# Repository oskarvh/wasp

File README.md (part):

# wasp

**WebAssembly Swarm Processor** — a WAMR network compute distribution for MCUs.

A *wasp node* is a deliberately dumb MCU: it boots Zephyr, joins the network,
and waits. A *coordinator* (future work, not in this repo yet) pushes
WebAssembly modules and execution commands to nodes over a TCP socket. The
node loads the module into the [WebAssembly Micro Runtime
(WAMR)](https://github.com/bytecodealliance/wasm-micro-runtime), executes it,
and reports results back. All application intelligence lives in the WASM
modules and the coordinator — the firmware is a thin, portable execution
shell.

```
┌─────────────┐        TCP / framed protocol         ┌──────────────────────┐
│ Coordinator │ ───────────────────────────────────▶ │  wasp node (MCU)     │
│ (future)    │ ◀─────────────────────────────────── │  Zephyr + WAMR       │
└─────────────┘      results / logs / status         └──────────────────────┘
                                                        … × N nodes (swarm)
```

## Firmware architecture

The firmware is a Zephyr application with three long-lived threads connected
by message queues. Ownership is strict: only the network thread touches the
socket, only the executor thread calls into a running WASM module.

```
                         wasp node firmware
┌─────────────────────────────────────────────────────────────────────┐
│                                                                     │
│  ┌───────────────┐  rx msgq   ┌──────────────┐  exec q  ┌─────────┐ │
│  │ network       │ ─────────▶ │ agent        │ ───────▶ │ wasm    │ │
│  │ handler       │            │              │          │ executor│ │
│  │ thread        │ ◀───────── │ • protocol   │          └───┬─────┘ │
│  └───────┬───────┘  tx msgq   │   dispatch   │              │       │
│          │             ▲      │ • routing    │        WAMR runtime  │
│   Zephyr network stack │      └──────────────┘        (interpreter, │
│   (sockets, DHCP)      └─────────────────────────────  static heap  │
│          │                 responses from executor     pool) +      │
│   Ethernet driver (per-board)                          module       │
│                                                        lifecycle    │
└─────────────────────────────────────────────────────────────────────┘
```

### Threads

| Thread              | Responsibility                                                                                                                              |
| ------------------- | ------------------------------------------------------------------------------------------------------------------------------------------- |
| **network handler** | Brings up the network interface (DHCP by default), runs the TCP server socket, frames/deframes protocol messages, forwards complete commands to the agent via the rx queue, and drains the tx queue back to the coordinator. Owns the socket exclusively. Framing-level errors (bad magic, oversize, no memory) are handled here. |
| **agent**           | Protocol dispatcher. Answers protocol-level commands (HELLO, PING) itself and routes WASM lifecycle commands (LOAD_MODULE / UNLOAD_MODULE / CALL) to the executor via the exec queue. Never blocks on WASM execution. |
| **wasm executor**   | The **only** thread that touches the WAMR runtime. Consumes lifecycle and call requests from the exec queue — serialized, so a module can never be unloaded mid-call — and posts responses directly to the tx queue. Isolated in its own thread so a long-running or misbehaving module cannot wedge the agent or the network handler. |

Zephyr's own threads (net stack rx/tx, system workqueue, logging) run
alongside these.

### Message flow

1. Coordinator connects and sends a framed command (e.g. *load module*,
   *call function*).
2. Network handler validates the frame and posts it to the **rx msgq**.
3. Agent answers protocol commands directly on the **tx msgq**; lifecycle
   and call commands are routed (payload ownership included) to the
   **exec queue**.
4. Executor performs the runtime operation and posts the RESULT/ERROR
   response directly to the **tx msgq**.
5. Network handler drains the tx msgq onto the socket.

### Wire protocol

Length-prefixed binary frames over a single TCP connection (default port
`4242`, configurable via Kconfig). Canonical definition:
`app/src/protocol.h`; reference implementation of the coordinator side:
`tools/wasp_client.py`. Sequence diagrams for every command and failure
path: [docs/diagrams/](docs/diagrams/README.md).

```
┌────────┬────────┬───────────┬─────────────┬───────────┐
│ "WA"   │ type   │ seq       │ payload len │ payload   │
│ 2 B    │ 1 B    │ 1 B       │ 4 B LE      │ n B       │
└────────┴────────┴───────────┴─────────────┴───────────┘
```

Responses echo the request's `seq`. Payloads are capped at
`CONFIG_WASP_MAX_MODULE_SIZE`, advertised in `HELLO_ACK`; oversized frames
are drained and answered with `ERROR(TOO_LARGE)` without losing stream
sync. A bad magic means the stream is desynchronized and the node drops
the connection.

Command set:

- `HELLO` / `HELLO_ACK` — version exchange; ack carries the payload cap
  and feature bits (`0x01` remote memory, `0x02` atomic primitives)
- `LOAD_MODULE` — payload is a `.wasm` binary; node loads + instantiates it
  (one module at a time; ack is an empty `RESULT`)
- `UNLOAD_MODULE` — tears the module down and frees its memory
- `CALL` — `[name_len u8][name][argc u8][arg u32 LE × argc]`; invokes an
  exported function. v1 calling convention: **i32 args/results only**,
  signature-checked on the node via WAMR introspection
- `RESULT` — `[nresults u8][value u32 LE × n]` (empty for lifecycle acks)
- `ERROR` — `[code u8][optional utf8 detail]`, e.g. `TRAP(wasm operand
  stack overflow)`; codes in `app/src/protocol.h`
- `PING` / `PONG` — liveness; `PONG` echoes the `PING` payload
- `IDENTIFY` — strobes the status LED (default 10 s) so a human can find
  the physical board: `wasp_client.py <ip> identify [seconds]`
- `REBOOT` — remote reboot; mode 1 enters the USB bootloader (RP2040
  only), so Pico Ws can be reflashed without touching BOOTSEL:
  `wasp_client.py <ip> reboot [--bootsel]`
- `MEM_READ` / `MEM_WRITE` / `LOCK` / `UNLOCK` / `REGION_INFO` /
  `MEM_ADD` / `MEM_CAS` (0x4x) — **node-initiated** remote-memory
  requests, sent mid-`CALL` in the node's own seq space and answered by
  the coordinator; see [Remote memory](#remote-memory--design-plan)

A module that traps (e.g. `unreachable`, out-of-bounds access) returns
`ERROR(TRAP, exception-text)` and the node carries on — the WASM sandbox
holds, and the next `CALL` works.

### Discovery & status LED

Nodes don't need to be known in advance: once online, every node
broadcasts an `ANNOUNCE` datagram to UDP port `4243` every 5 seconds
(both Kconfig-tunable) carrying its protocol version, feature bits, TCP
port, busy flag (coordinator currently connected) and board name.

```
python3 tools/wasp_client.py discover            # human-readable list
python3 tools/wasp_client.py discover --ips      # for scripting
python3 tools/swarm_test.py tools/remote_module.wasm discover
```

Boards with an `led0` devicetree alias (the Nucleo's green LED, the Pico
W's WiFi-chip LED — wired up in the app overlay) show their state at a
glance:

| Pattern | Meaning |
| --- | --- |
| fast blink (5 Hz) | no network yet (WiFi joining / DHCP) |
| heartbeat (short blip every second) | online, waiting for a coordinator |
| solid on | coordinator connected |
| frantic strobe (10 Hz) | `IDENTIFY` received — "here I am" |

Broadcast datagrams do not cross routers, so `ANNOUNCE` discovery is
LAN-only by nature. Reaching a coordinator on another network is a
planned expansion (unicast registration to a DNS-resolved coordinator
hostname — see the roadmap); DNS-based tricks cannot make an actual
*broadcast* leave the LAN.

### Memory strategy

WAMR runs from a **static heap pool** (`Alloc_With_Pool`) so WASM memory is
bounded and isolated from the Zephyr kernel heap. Pool size, thread stack
sizes, and the maximum module size are Kconfig options tuned per board.

The pool must live in **main SRAM** and comfortably exceed 64 KiB: a WASM
page is fixed at 64 KiB, so instantiating any standard clang-built module
demands one contiguous 64 KiB+ allocation for its linear memory. The
payload heap (protocol buffers + the raw `.wasm` of the loaded module)
takes the board's tightly-coupled memory instead when available — on the
F439: 88 KiB SRAM pool for WAMR, 40 KiB payload heap in CCM.

## Repository layout

```
wasp/
├── app/                    # the Zephyr application (manifest repo for west)
│   ├── west.yml            # pins Zephyr, HALs, and WAMR
│   ├── CMakeLists.txt
│   ├── Kconfig             # wasp-specific options (port, pool sizes, …)
│   ├── prj.conf            # board-agnostic configuration
│   ├── boards/             # per-board config & devicetree overlays
│   │   └── nucleo_f439zi.conf
│   └── src/
│       ├── main.c          # boot, queue setup, thread start
│       ├── led.c           # status LED thread (patterns + IDENTIFY strobe)
│       ├── rpc.c           # node->coordinator RPC slot (remote memory)
│       ├── net/            # net bring-up (netup.c) + worker socket/framing + ANNOUNCE
│       ├── agent/          # agent thread + protocol dispatch
│       ├── wamr/           # WAMR wrapper + executor + wasp.* host functions
│       └── peer/           # peer role: host-function API (peer_api.h), conductor
│                           #   demo, boot smoke test — libwasp in firmware
├── deps/                   # west-managed dependencies (NOT committed)
│   ├── zephyr/
│   └── modules/            # hal_stm32, cmsis, wasm-micro-runtime, …
├── docs/
│   ├── writing-modules.md  # C function -> node -> result, step by step
│   ├── performance.md      # measured remote-memory costs + optimization guide
│   ├── demo.md             # the distributed Mandelbrot demo, explained
│   ├── hardware.md         # design notes for a future purpose-built node board
│   ├── coordinator.md      # libwasp C library + peer load-sharing design sketch
│   └── diagrams/           # PlantUML sequence diagrams for every protocol scenario
├── libwasp/                # the coordinator as a C library (docs/coordinator.md)
│   ├── include/wasp/libwasp.h  # public API: ctx, nodes, regions, locks, events
│   ├── src/                # OS-free core + memory host; port_posix.c / port_zephyr.c
│   ├── test/mock_test.c    # scripted fake-node test (`make check`, no hardware)
│   └── Makefile            # POSIX build: libwasp.so
├── tools/
│   ├── wasp_client.py      # pure-Python reference client + remote-memory host
│   ├── libwasp.py          # ctypes binding: wasp_client-compatible WaspNode over libwasp
│   ├── libwasp_selftest.py # runs wasp_client's test suites through the C library
│   ├── swarm_test.py       # multi-node concurrency test (distributed sum, race,
│   │                       #   fail-fast vs queued locks vs atomic MEM_ADD)
│   ├── include/wasp/remote.h   # module-side remote memory API (C)
│   ├── include/wasp/remote.hpp # remote_ptr<T> / remote_lock (C++, no plugin)
│   ├── wasp-remote-pass/   # LLVM pass plugin: lowers wasp_remote dereferences
│   ├── lib/wasp_remote_rt.c    # runtime shims the pass lowers into
│   ├── perf_test.py        # remote-memory performance characterization (docs/performance.md)
│   ├── mandelbrot_demo.py  # distributed-render demo coordinator (docs/demo.md)
│   ├── test_module.c       # test WASM module (add/fib/boom)
│   ├── remote_module.c     # remote-memory test module (explicit API)
│   ├── perf_module.c       # performance-measurement module (driven by perf_test.py)
│   ├── mandelbrot_module.c # fixed-point Mandelbrot kernel + work-stealing loop
│   ├── remote_as_module.c  # transparent wasp_remote pointer test module
│   ├── remote_cpp_module.cpp   # C++ remote_ptr test module
│   └── build_test_module.sh
└── README.md
```

External code (Zephyr, STM32 HAL, WAMR) is pulled by **west** from the
manifest in `app/west.yml`, pinned to exact release tags — same
reproducibility as git submodules, but west also resolves Zephyr's internal
module graph, which plain submodules cannot. `deps/` is gitignored.

## Portability

Nothing in `src/` may include board- or SoC-specific headers. Portability is
handled by the Zephyr layers:

- **Board selection** is a build-time switch: `west build -b <board> app`.
- **Per-board tuning** (heap pool size, network driver options, devicetree
  overlays) lives in `app/boards/<board>.conf` / `.overlay`.
- **New MCU support** = add a board conf/overlay (and a HAL module to the
  manifest allowlist if it's a new vendor). No source changes.

Supported boards:

- **wasp node board** (`wasp_node`) — the purpose-built board: STM32H723ZG
  Cortex-M7 @ 550 MHz, 320 KiB AXI SRAM, a KSZ8794 3-port switch so nodes
  daisy-chain without external switches, and three instance slots. Board
  definition lives in-tree at `boards/wasp/wasp_node`, so no `BOARD_ROOT`
  needs setting — `app/CMakeLists.txt` points at it. Design rationale:
  [docs/hardware.md](docs/hardware.md).
- **ST Nucleo-F439ZI** (`nucleo_f439zi`) — Cortex-M4F @ 180 MHz, 192 KiB
  SRAM + 64 KiB CCM, on-board Ethernet (LAN8742 PHY).
- **Raspberry Pi Pico W** (`rpi_pico/rp2040/w`) — Cortex-M0+ @ 133 MHz,
  264 KiB SRAM, CYW43439 WiFi (Infineon AIROC driver; needs a one-time
  `west blobs fetch hal_infineon` and WiFi credentials, see
  [Building](#building)). Console is USB CDC-ACM. WAMR runs the generic
  soft-float `THUMB` target on ARMv6-M.

## Building

Dependencies: CMake ≥ 3.20, Python ≥ 3.10, a toolchain (Zephyr SDK, or GNU
Arm Embedded with `ZEPHYR_TOOLCHAIN_VARIANT=gnuarmemb`).

```sh
# one-time workspace setup (from the repo root)
python3 -m venv .venv && source .venv/bin/activate
pip install west ninja
west init -l app
west update                # clones Zephyr + WAMR into deps/
pip install -r deps/zephyr/scripts/requirements-base.txt

# if using GNU Arm Embedded instead of the Zephyr SDK:
export ZEPHYR_TOOLCHAIN_VARIANT=gnuarmemb
export GNUARMEMB_TOOLCHAIN_PATH=/usr   # prefix of arm-none-eabi-gcc

# build & flash — wasp node board (Ethernet via its own switch)
west build -b wasp_node app -d build/node
west flash -d build/node   # openocd over an ST-Link V2 on the SWD header (J6)

# build & flash — Nucleo-F439ZI (Ethernet)
west build -b nucleo_f439zi app
west flash                 # needs stlink (openocd or STM32CubeProgrammer)

# build & flash — Raspberry Pi Pico W (WiFi)
west blobs fetch hal_infineon                   # one-time: CYW43439 firmware
cp app/wifi_credentials.conf.example app/wifi_credentials.conf
#   ...then edit app/wifi_credentials.conf with your SSID/PSK. The file is
#   gitignored and merged into the build automatically whenever it exists.
west build -b rpi_pico/rp2040/w app -d build/pico
west flash -d build/pico -r uf2                 # board must be in BOOTSEL mode
```

The BOOTSEL-button dance (hold it while plugging in) is only needed the
**first** time a Pico is flashed with wasp. From then on, reflash over
the network:

```sh
python3 tools/wasp_client.py <node-ip> reboot --bootsel   # RP2040 only
# ...the RPI-RP2 drive enumerates over USB; mount it and copy the image:
cp build/pico/zephyr/zephyr.uf2 /media/$USER/RPI-RP2/
# node reboots into the new firmware and rejoins the network in ~20 s
```

### wasp node board notes

`west flash` uses openocd with `boards/wasp/wasp_node/support/openocd.cfg`,
which drives an ST-Link **V2** (`interface/stlink.cfg` plus
`dapdirect_swd`). That is deliberately not the Nucleo's configuration — the
in-tree Nucleo boards use `stlink-dap.cfg`, the V3 path, which a V2 will
not answer. For an older V2 or a clone, swap the transport line for
`hla_swd`; if your SWD pigtail omits NRST, use `reset_config none
separate`. Both are noted in the file.

**Reflashing over USB, no debugger.** The H723 has a DFU bootloader in
system memory, so the board can be flashed with nothing but a USB-C
cable. Two ways in:

```sh
# 1. the button: hold SW2 (BOOT0) and tap reset, then
dfu-util -a 0 -s 0x08000000:leave -D build/node/zephyr/zephyr.bin

# 2. over the network, no hands on the board (same flag the Picos use)
python3 tools/wasp_client.py <node-ip> reboot --bootsel
```

The second route leaves a magic word in uninitialised RAM, resets, and
jumps to the ROM bootloader from `PRE_KERNEL_1` priority 0 — ahead of the
clock driver, so the chip is still on its reset defaults rather than at
550 MHz on a PLL with caches and Ethernet DMA live. See the comment at the
top of `app/src/boot_dfu.c`.

Either way the board must be on USB-C **as a data link to the PC**: per
AN2606 the bootloader samples its interfaces and leaves for the
application when no host answers, and a charger or a power-only cable
looks exactly like no host. If the node boots normally instead of
appearing as `0483:df11`, the console says which of the two failures it
was.

Pass `-p` to `west build` after changing Kconfig or devicetree — Kconfig
results are cached and a plain rebuild will silently keep the old values.

The board has no USB-serial bridge of its own (a bare ST-Link V2 has no
VCP), so the console comes out on the expansion header: **J9.3 = PD8**
(board TX), **J9.4 = PD9** (board RX), plus a header ground, at 115200
8N1. Any 3V3 USB-TTL adapter will do. To use the board's own USB-C as a
CDC-ACM console instead:

```sh
west build -b wasp_node app -d build/node -- \
    -DEXTRA_CONF_FILE=boards/wasp_node_cdc.conf \
    -DEXTRA_DTC_OVERLAY_FILE=boards/wasp_node_cdc.overlay
```

A healthy boot looks like this — the switch line is the one to check
first, because port 4 comes out of reset in RGMII mode and nothing moves
until the firmware tells it RMII:

```
wasp_ksz: KSZ8794 found, rev 0
wasp_ksz: port 4: RMII, clock mode (0x56 = 0xed)
wasp_ksz: port 1 (J2): link up, autoneg done
wasp: sysclk 550 MHz from PLL1 (HSE ready, PLL1 locked), HCLK 275 MHz
wasp_wamr: WAMR initialized (pool: 249992 bytes, all spare RAM, ~3 instance(s))
wasp_netup: IPv4 address: 10.0.0.189
```

Ethernet goes to any of the three jacks — **J2 is switch port 1**, J4 is
port 2, J5 is port 3, and the driver logs which ones have a link three
seconds after boot. The external PSRAM is mapped but not used; see
[docs/hardware.md](docs/hardware.md) for why, and
`CONFIG_WASP_PSRAM_ALLOW`.

Talking to a node — no serial cable needed, nodes announce themselves
over UDP broadcast (see
[Discovery & status LED](#discovery--status-led)):

```sh
python3 tools/wasp_client.py discover               # list nodes on the LAN
python3 tools/wasp_client.py <node-ip> identify     # strobe LED: which board is this?
python3 tools/wasp_client.py <node-ip> check        # protocol self-test
tools/build_test_module.sh                          # needs clang + wasm-ld
python3 tools/wasp_client.py <node-ip> lifecycle tools/test_module.wasm
python3 tools/wasp_client.py <node-ip> load tools/test_module.wasm
python3 tools/wasp_client.py <node-ip> call fib 20
python3 tools/wasp_client.py <node-ip> unload
python3 tools/wasp_client.py <node-ip> reboot       # remote reboot (any board)
python3 tools/wasp_client.py <node-ip> reset        # release every module/instance
```

### Where the time goes

Nodes count, per instance, how long they spent inside the interpreter
against how long they spent waiting for the coordinator to answer a
remote-memory round trip. Host-side wall clock cannot tell those apart,
which is the whole reason the counters exist on the node.

```sh
python3 tools/wasp_client.py <node-ip> stats --reset   # zero
# ...run whatever you want to measure...
python3 tools/wasp_client.py <node-ip> stats           # read

python3 tools/mandelbrot_demo.py <ips...> --stats      # or let the demo do it
```

```
 inst  calls      exec   compute   waiting  wait%   RPCs  traffic
   16      1   585.3ms   180.6ms   404.7ms  69.1%     34     8.3K
    1      1   585.3ms   184.8ms   400.4ms  68.4%     34     8.3K
    2      1   587.7ms   185.0ms   402.7ms  68.5%     34     8.3K
  all      3     1.76s   550.4ms     1.21s  68.7%    102    24.9K
             per round trip: 11.8ms waiting, 249B moved
```

A round trip's wait is accrued *inside* the call that issued it, so
`compute = exec - waiting` and the split needs no second measurement.
Instance `gone` is the total for instances since dropped — releasing a
module would otherwise take its own measurements with it, which makes
"run a workload, then ask what happened" report nothing.

The per-round-trip line is the one to watch. Rendering the same frame
with one, two and three instances per node across two boards:

| inst/node | workers | compute/node | wait% | ms per round trip |
| ---: | ---: | ---: | ---: | ---: |
| 1 | 2 | 540 ms | 27.1% | 2.05 |
| 2 | 4 | 554 ms | 52.9% | 6.24 |
| 3 | 6 | 555 ms | 68.4% | 11.8 |

Compute per node is conserved, as it must be — same work, same core. But
the wait per round trip grows roughly linearly with the number of
concurrent workers, which is the signature of a serialized server rather
than of the wire: the coordinator services all remote memory behind one
mutex. That is the current ceiling, not the nodes — wall time is flat at
0.8 s whether a node runs one instance or three, and the core still sits
around a third idle at three.

WASM modules for wasp are plain clang output — no SDK required:

```sh
clang --target=wasm32 -O2 -nostdlib -Wl,--no-entry -Wl,--export-dynamic \
      -z stack-size=1024 -o module.wasm module.c
```

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
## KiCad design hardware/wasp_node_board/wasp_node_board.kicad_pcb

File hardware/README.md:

# wasp node board

KiCad 9 project for the purpose-built wasp node: STM32H723ZGT6 + octal-bus
PSRAM + a KSZ8794CNX switch giving every node three copper ports, so a fleet
cables itself into a tree instead of fanning out to a desk switch.

The design rationale — part choices, what was rejected and why, the power and
clocking decisions, and the gotchas that cost real time — lives in
[`docs/hardware.md`](../docs/hardware.md). The block diagram is
[`docs/diagrams/node-board.svg`](../docs/diagrams/node-board.svg).

Open `wasp_node_board/wasp_node_board.kicad_pro`. Sheets: `mcu`, `power`,
`eth`.

## External libraries are not committed

`hardware/lib/` is gitignored. The parts in it come from third-party symbol
services whose terms on redistributing the library files are unclear, so the
repo records **where to re-fetch them** instead of vendoring them.

This costs less than it sounds: KiCad caches symbol definitions inline in each
`.kicad_sch`, so the schematic opens, renders and netlists on a fresh clone
with no libraries present. It is **footprints** that go missing, which matters
only once PCB layout starts.

Layout convention, matching the project library tables:

```
hardware/lib/<PART>/<PART>.kicad_sym     # symbol
hardware/lib/<PART>/<PART>.kicad_mod     # footprint (or <PART>.pretty/)
```

The project's `sym-lib-table` and `fp-lib-table` reference these through
`${KIPRJMOD}/../lib/...`, so they resolve wherever the repo is checked out.

### What to re-fetch

| ref | part | source |
| --- | --- | --- |
| U1 (eth) | Microchip `KSZ8794CNXCC` | [SnapEDA](https://www.snapeda.com/parts/KSZ8794CNXCC/Microchip/view-part) |
| FL1 | TDK `ACM2012-361-2P-T002` | [Ultra Librarian](https://app.ultralibrarian.com/details/55ef4603-1073-11e9-ab3a-0a3560a4cccc/TDK/ACM2012-361-2P-T002) |
| J3 | GCT `USB4110-GF-A` | [Ultra Librarian](https://app.ultralibrarian.com/details/3db0fb39-9b49-11ea-b5d0-0aebb021a1ea/Global-Connector-Technology/USB4110-GF-A) |
| U4 | TI `TPSM863253RDXR` | [Ultra Librarian](https://app.ultralibrarian.com/details/232cd2f6-c430-11ee-8cb3-0ae0a3b49db5/Texas-Instruments/TPSM863253RDXR) |

Install each under `hardware/lib/<PART>/` and register it in the project
library tables. Everything else on the board comes from stock KiCad libraries
and needs no fetching.

## Known gaps before layout

**J3's symbol and footprint do not match.** The schematic still uses the
cached 20-pin SamacSys symbol (`A1 A4 … B12`, `MP1`–`MP4`), while the
registered Ultra Librarian footprint uses **merged** pads — `A1-B12`,
`A4-B9`, `A9-B4`, `A12-B1`, plus `13`–`18` for the shell. Every VBUS, ground
and shield pin therefore has no pad to land on, and layout will fail on
twelve of them.

The fix is to drop the external library for J3 entirely and use stock KiCad,
which carries this exact receptacle:

| | |
| --- | --- |
| symbol | `Connector:USB_C_Receptacle_USB2.0_16P` |
| footprint | `Connector_USB:USB_C_Receptacle_GCT_USB4110` |

Both use `A1 A4 A5 A6 A7 A8 A9 A12 B1 B4 B5 B6 B7 B8 B9 B12 S1`, so they pair
exactly — and that is the same separate-pin naming the schematic is already
wired against, so only the shell connection changes (`MP1`–`MP4` → `S1`).
Using Ultra Librarian's own 12-pin symbol with its merged footprint would also
be coherent, but means re-wiring VBUS and ground onto merged pins for no gain.

While J3 is open: `DP1`/`DP2` (A6/B6) and `DN1`/`DN2` (A7/B7) stay separate
pins on the stock symbol, so tying them pairwise for cable-flip independence
is still an explicit job in the schematic.

**FL1 and U4 are cosmetic only.** Both cached symbols were diffed against the
installed libraries pin-by-pin and are identical — 4 pins for the choke, 7 for
the buck module — so the TPSM863**252**-vs-**253** and ACM2012-**201**-vs-**361**
mismatches carry no electrical risk. Values on the schematic are already
correct, so a BOM export is right either way. Registering the two `.kicad_sym`
files and re-linking is worth doing for traceability, not urgency.

The KSZ8794's footprint may not need the external library at all: stock KiCad
ships `Package_DFN_QFN:QFN-64-1EP_8x8mm_P0.4mm_EP6.5x6.5mm` (and a
`_ThermalVias` variant, which a QFN exposed pad wants). If §11 of the datasheet
confirms a 6.5 × 6.5 mm exposed pad, switching to the stock footprint leaves
only the symbol as third-party — and the PCB is still empty, so this is the
cheapest moment to make that swap.

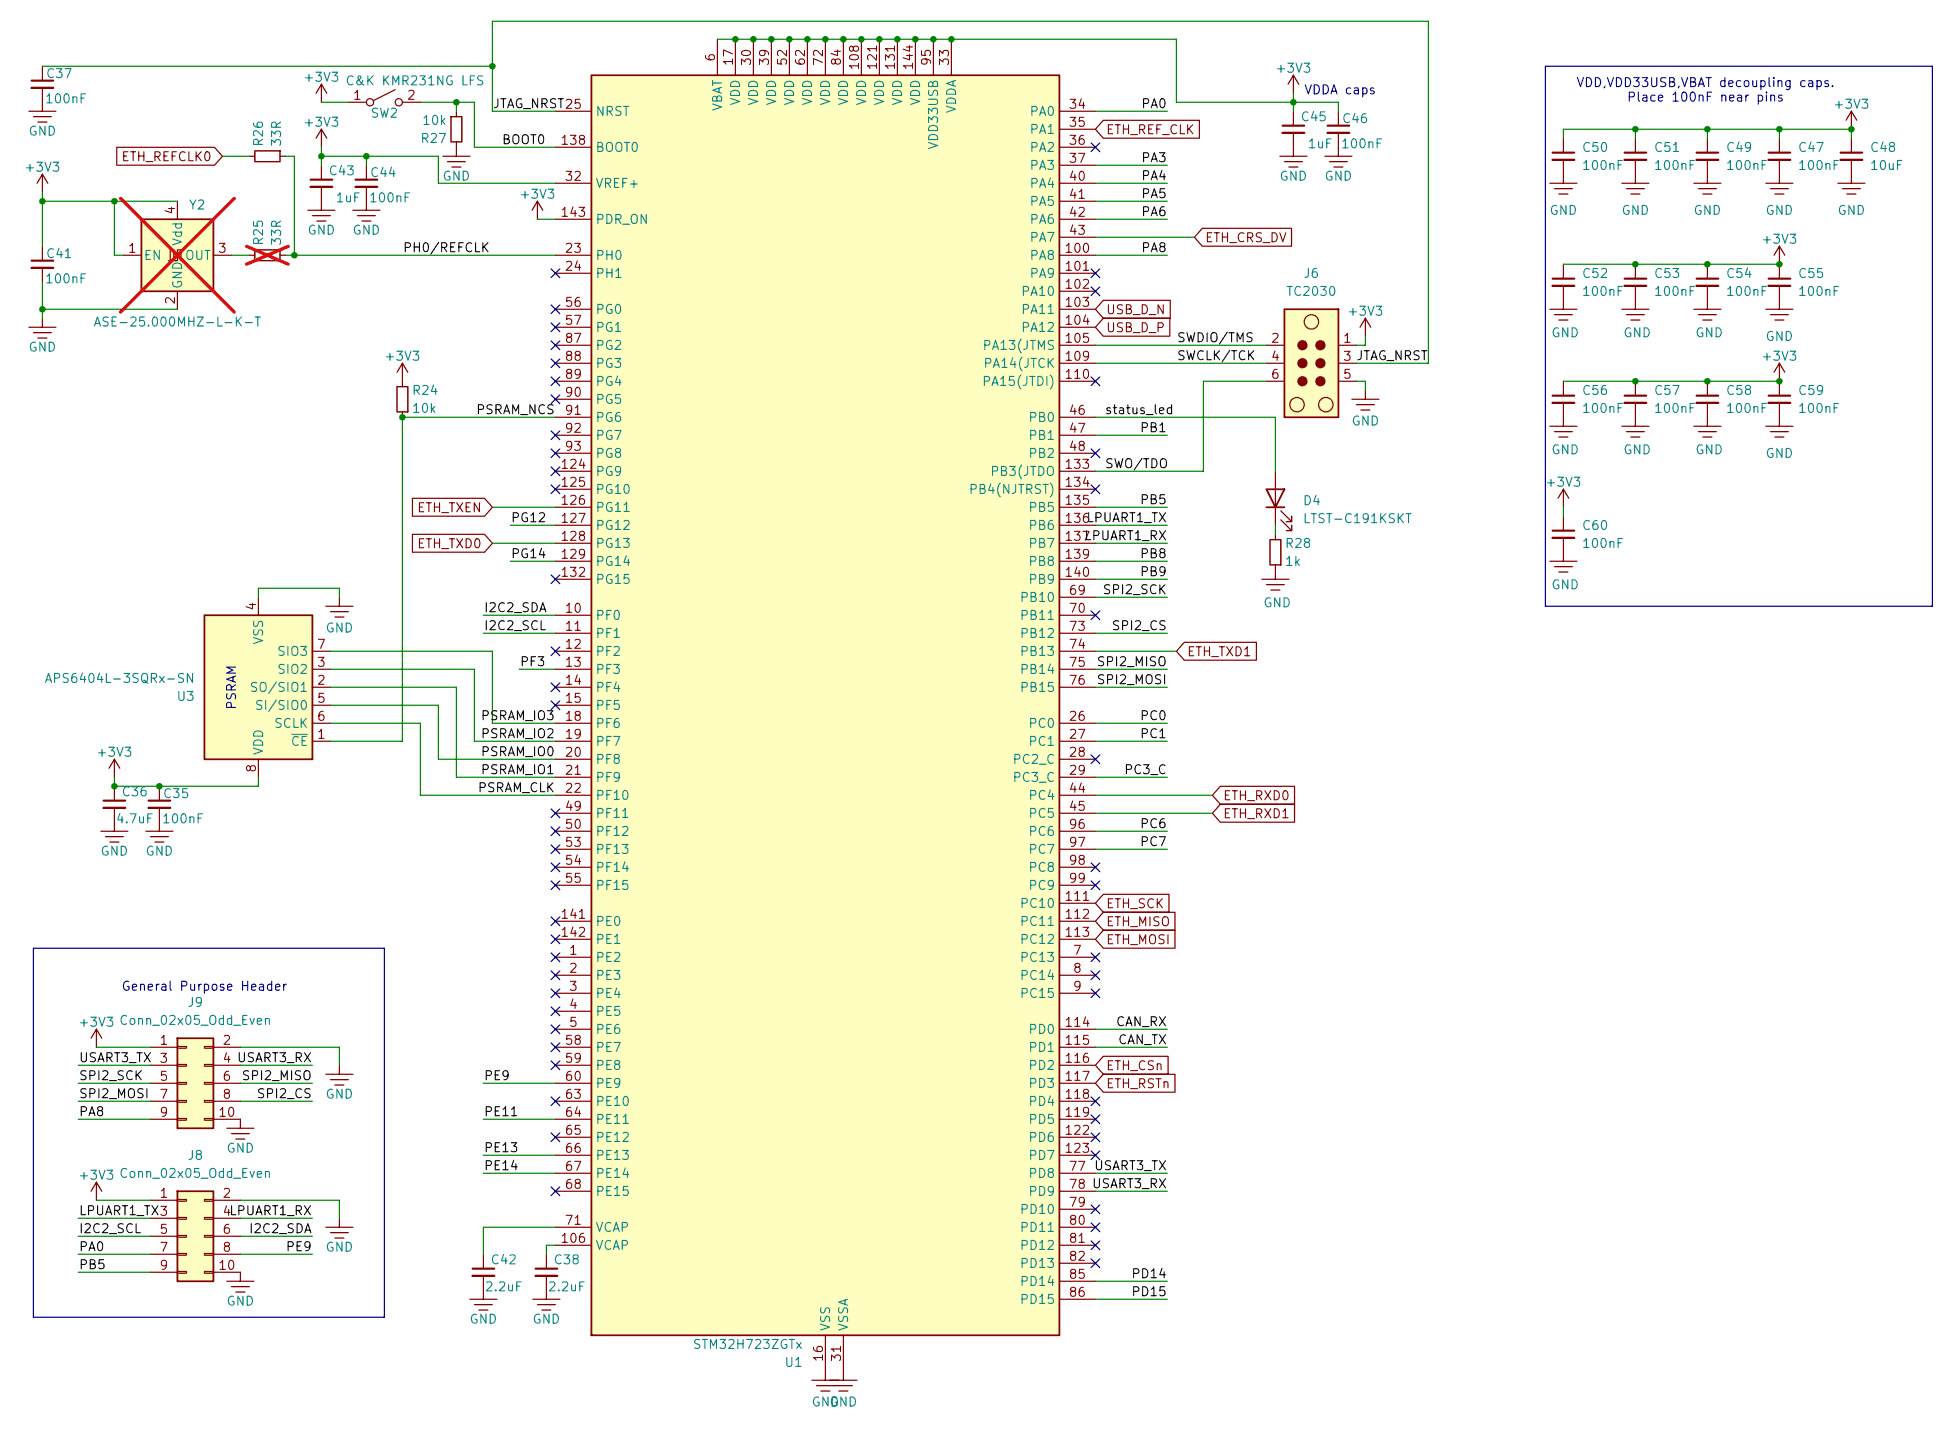
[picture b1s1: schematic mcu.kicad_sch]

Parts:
C35, C37, C41, C44, C46: 100nF; C_0402_1005Metric
C36: 4.7uF; C_0603_1608Metric
C38, C42: 2.2uF; C_0603_1608Metric
C43, C45: 1uF; C_0603_1608Metric
C47, C49, C50, C51, C52, C53, C54, C55, C56, C57, C58, C59, C60: 100nF; C_0402_1005Metric; LCSC C1525
C48: 10uF; C_0805_2012Metric; LCSC C15850
D4: LTST-C191KSKT; LED_0603_1608Metric
J6: TC2030; Tag-Connect_TC2030-IDC-NL_2x03_P1.27mm_Vertical
J8, J9: Conn_02x05_Odd_Even; PinHeader_2x05_P2.54mm_Vertical_SMD
R24, R27: 10k; R_0402_1005Metric; LCSC C140214
R25: 33R; R_0402_1005Metric; LCSC C140214; not fitted
R26: 33R; R_0402_1005Metric; LCSC C140214
R28: 1k; R_0402_1005Metric; LCSC C140214
SW2: C&K KMR231NG LFS; SW_Push_1P1T_NO_CK_KMR2
U1: STM32H723ZGTx; LQFP-144_20x20mm_P0.5mm
U3: APS6404L-3SQRx-SN; SOIC-8_3.9x4.9mm_P1.27mm
Y2: ASE-25.000MHZ-L-K-T; Oscillator_SMD_Abracon_ASE-4Pin_3.2x2.5mm; not fitted

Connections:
+3V3: C35.1, C36.1, C41.1, C43.1, C44.1, C45.1, C46.1, C47.1, C48.1, C49.1, C50.1, C51.1, C52.1, C53.1, C54.1, C55.1, C56.1, C57.1, C58.1, C59.1, C60.1, J6.1, J8.1, J9.1, R24.2, SW2.1 (A), U1.6 (VBAT), U1.17 (VDD), U1.30 (VDD), U1.32 (VREF+), U1.33 (VDDA), U1.39 (VDD), U1.52 (VDD), U1.62 (VDD), U1.72 (VDD), U1.84 (VDD), U1.95 (VDD33USB), U1.108 (VDD), U1.121 (VDD), U1.131 (VDD), U1.143 (PDR_ON), U1.144 (VDD), U3.8 (VDD), Y2.1 (EN), Y2.4 (Vdd); also elsewhere on the board
/mcu/BOOT0: R27.1, SW2.2 (B), U1.138 (BOOT0)
/mcu/CAN_RX: U1.114 (PD0)
/mcu/CAN_TX: U1.115 (PD1)
/mcu/I2C2_SCL: J8.5, U1.11 (PF1)
/mcu/I2C2_SDA: J8.6, U1.10 (PF0)
/mcu/JTAG_NRST: C37.1, J6.3, U1.25 (NRST)
/mcu/LPUART1_RX: J8.4, U1.137 (PB7)
/mcu/LPUART1_TX: J8.3, U1.136 (PB6)
/mcu/PA0: J8.7, U1.34 (PA0)
/mcu/PA3: U1.37 (PA3)
/mcu/PA4: U1.40 (PA4)
/mcu/PA5: U1.41 (PA5)
/mcu/PA6: U1.42 (PA6)
/mcu/PA8: J9.9, U1.100 (PA8)
/mcu/PB1: U1.47 (PB1)
/mcu/PB5: J8.9, U1.135 (PB5)
/mcu/PB8: U1.139 (PB8)
/mcu/PB9: U1.140 (PB9)
/mcu/PC0: U1.26 (PC0)
/mcu/PC1: U1.27 (PC1)
/mcu/PC3_C: U1.29 (PC3_C)
/mcu/PC6: U1.96 (PC6)
/mcu/PC7: U1.97 (PC7)
/mcu/PD14: U1.85 (PD14)
/mcu/PD15: U1.86 (PD15)
/mcu/PE9: J8.8, U1.60 (PE9)
/mcu/PE11: U1.64 (PE11)
/mcu/PE13: U1.66 (PE13)
/mcu/PE14: U1.67 (PE14)
/mcu/PF3: U1.13 (PF3)
/mcu/PG12: U1.127 (PG12)
/mcu/PG14: U1.129 (PG14)
/mcu/PH0/REFCLK: R25.1, R26.1, U1.23 (PH0)
/mcu/PSRAM_CLK: U1.22 (PF10), U3.6 (SCLK)
/mcu/PSRAM_IO0: U1.20 (PF8), U3.5 (SI/SIO0)
/mcu/PSRAM_IO1: U1.21 (PF9), U3.2 (SO/SIO1)
/mcu/PSRAM_IO2: U1.19 (PF7), U3.3 (SIO2)
/mcu/PSRAM_IO3: U1.18 (PF6), U3.7 (SIO3)
/mcu/PSRAM_NCS: R24.1, U1.91 (PG6), U3.1 (~CE)
/mcu/SPI2_CS: J9.8, U1.73 (PB12)
/mcu/SPI2_MISO: J9.6, U1.75 (PB14)
/mcu/SPI2_MOSI: J9.7, U1.76 (PB15)
/mcu/SPI2_SCK: J9.5, U1.69 (PB10)
/mcu/SWCLK/TCK: J6.4, U1.109 (PA14(JTCK)
/mcu/SWDIO/TMS: J6.2, U1.105 (PA13(JTMS)
/mcu/SWO/TDO: J6.6, U1.133 (PB3(JTDO)
/mcu/USART3_RX: J9.4, U1.78 (PD9)
/mcu/USART3_TX: J9.3, U1.77 (PD8)
/mcu/status_led: D4.2 (A), U1.46 (PB0)
ETH_CRS_DV: U1.43 (PA7); also elsewhere on the board
ETH_CSn: U1.116 (PD2); also elsewhere on the board
ETH_MISO: U1.112 (PC11); also elsewhere on the board
ETH_MOSI: U1.113 (PC12); also elsewhere on the board
ETH_REFCLK0: R26.2; also elsewhere on the board
ETH_REF_CLK: U1.35 (PA1); also elsewhere on the board
ETH_RSTn: U1.117 (PD3); also elsewhere on the board
ETH_RXD0: U1.44 (PC4); also elsewhere on the board
ETH_RXD1: U1.45 (PC5); also elsewhere on the board
ETH_SCK: U1.111 (PC10); also elsewhere on the board
ETH_TXD0: U1.128 (PG13); also elsewhere on the board
ETH_TXD1: U1.74 (PB13); also elsewhere on the board
ETH_TXEN: U1.126 (PG11); also elsewhere on the board
GND: C35.2, C36.2, C37.2, C38.2, C41.2, C42.2, C43.2, C44.2, C45.2, C46.2, C47.2, C48.2, C49.2, C50.2, C51.2, C52.2, C53.2, C54.2, C55.2, C56.2, C57.2, C58.2, C59.2, C60.2, J6.5, J8.2, J8.10, J9.2, J9.10, R27.2, R28.1, U1.16 (VSS), U1.31 (VSSA), U1.38 (VSS), U1.51 (VSS), U1.61 (VSS), U1.83 (VSS), U1.94 (VSS), U1.107 (VSS), U1.120 (VSS), U1.130 (VSS), U3.4 (VSS), Y2.2 (GND); also elsewhere on the board
unnamed: C38.1, U1.106 (VCAP)
unnamed: C42.1, U1.71 (VCAP)
unnamed: D4.1 (K), R28.2
unnamed: R25.2, Y2.3 (OUT)
USB_D_N: U1.103 (PA11); also elsewhere on the board
USB_D_P: U1.104 (PA12); also elsewhere on the board

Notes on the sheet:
General Purpose Header
PSRAM
VDD,VDD33USB,VBAT decoupling caps. Place 100nF near pins
VDDA caps

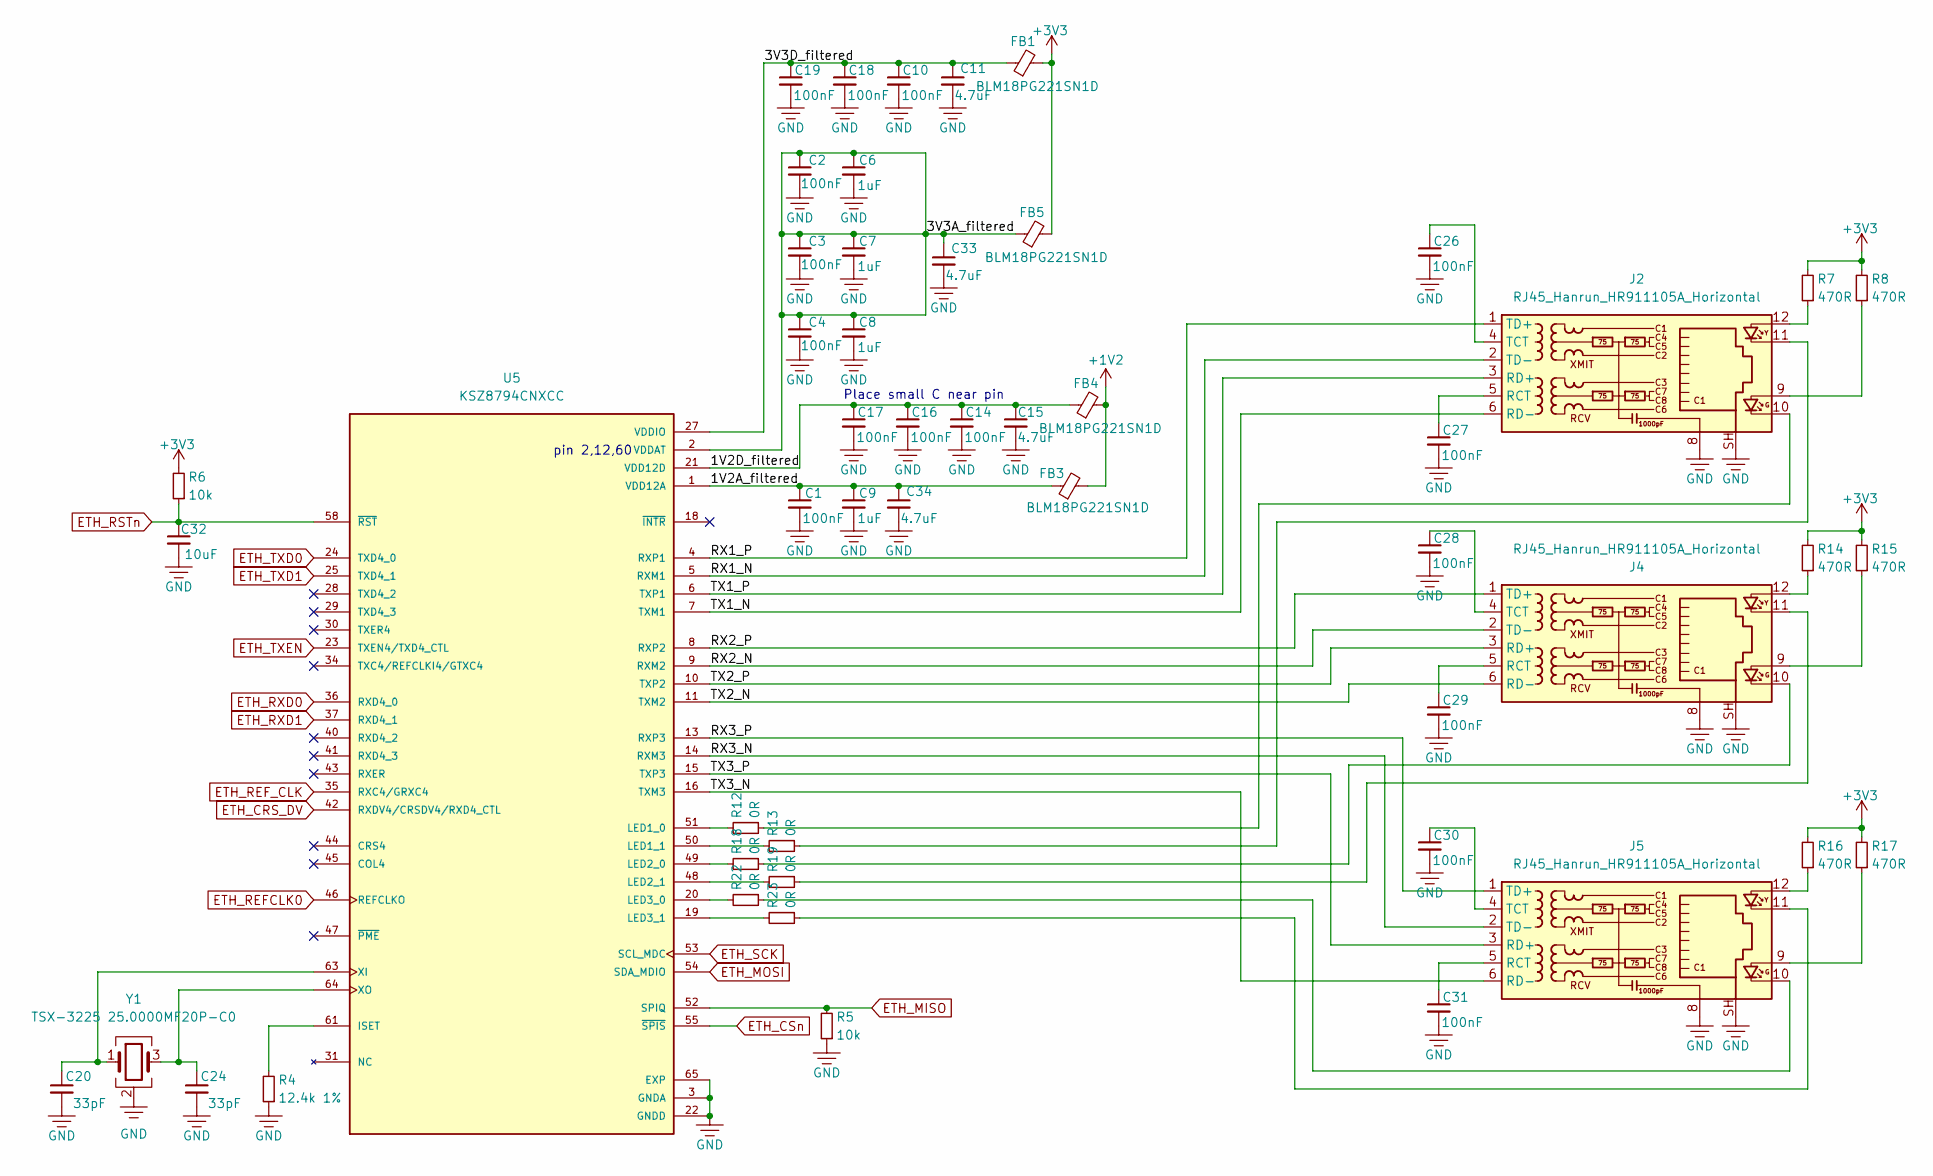
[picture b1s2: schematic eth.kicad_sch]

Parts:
C1, C2, C3, C4, C10, C14, C16, C17, C18, C19, C26, C27, C28, C29, C30, C31: 100nF; C_0402_1005Metric
C6, C7, C8, C9: 1uF; C_0603_1608Metric
C11, C15, C33, C34: 4.7uF; C_0603_1608Metric
C20, C24: 33pF; C_0402_1005Metric
C32: 10uF; C_0603_1608Metric
FB1, FB3, FB4, FB5: BLM18PG221SN1D; L_0603_1608Metric
J2, J4, J5: RJ45_Hanrun_HR911105A_Horizontal
R4: 12.4k 1%; R_0402_1005Metric; LCSC C140214
R5, R6: 10k; R_0402_1005Metric; LCSC C140214
R7, R8, R14, R15, R16, R17: 470R; R_0402_1005Metric; LCSC C140214
R12, R13, R18, R19, R22, R23: 0R; R_0402_1005Metric; LCSC C140214
U5: KSZ8794CNXCC; IC_KSZ8794CNXCC; PARTREV DS00002134E
Y1: TSX-3225 25.0000MF20P-C0; Crystal_SMD_3225-4Pin_3.2x2.5mm_HandSoldering

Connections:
+1V2: FB3.2, FB4.2; also elsewhere on the board
+3V3: FB1.2, FB5.2, R6.2, R7.2, R8.2, R14.2, R15.2, R16.2, R17.2; also elsewhere on the board
/ethernet/1V2A_filtered: C1.1, C9.1, C34.1, FB3.1, U5.1 (VDD12A)
/ethernet/RX1_N: J2.2 (TD-), U5.5 (RXM1)
/ethernet/RX1_P: J2.1 (TD+), U5.4 (RXP1)
/ethernet/RX2_N: J4.2 (TD-), U5.9 (RXM2)
/ethernet/RX2_P: J4.1 (TD+), U5.8 (RXP2)
/ethernet/RX3_N: J5.2 (TD-), U5.14 (RXM3)
/ethernet/RX3_P: J5.1 (TD+), U5.13 (RXP3)
/ethernet/TX1_N: J2.6 (RD-), U5.7 (TXM1)
/ethernet/TX1_P: J2.3 (RD+), U5.6 (TXP1)
/ethernet/TX2_N: J4.6 (RD-), U5.11 (TXM2)
/ethernet/TX2_P: J4.3 (RD+), U5.10 (TXP2)
/ethernet/TX3_N: J5.6 (RD-), U5.16 (TXM3)
/ethernet/TX3_P: J5.3 (RD+), U5.15 (TXP3)
ETH_CRS_DV: U5.42 (RXDV4/CRSDV4/RXD4_CTL); also elsewhere on the board
ETH_CSn: U5.55 (~SPIS); also elsewhere on the board
ETH_MISO: R5.2, U5.52 (SPIQ); also elsewhere on the board
ETH_MOSI: U5.54 (SDA_MDIO); also elsewhere on the board
ETH_REFCLK0: U5.46 (REFCLKO); also elsewhere on the board
ETH_REF_CLK: U5.35 (RXC4/GRXC4); also elsewhere on the board
ETH_RSTn: C32.1, R6.1, U5.58 (~RST); also elsewhere on the board
ETH_RXD0: U5.36 (RXD4_0); also elsewhere on the board
ETH_RXD1: U5.37 (RXD4_1); also elsewhere on the board
ETH_SCK: U5.53 (SCL_MDC); also elsewhere on the board
ETH_TXD0: U5.24 (TXD4_0); also elsewhere on the board
ETH_TXD1: U5.25 (TXD4_1); also elsewhere on the board
ETH_TXEN: U5.23 (TXEN4/TXD4_CTL); also elsewhere on the board
GND: C1.2, C2.2, C3.2, C4.2, C6.2, C7.2, C8.2, C9.2, C10.2, C11.2, C14.2, C15.2, C16.2, C17.2, C18.2, C19.2, C20.2, C24.2, C26.2, C27.2, C28.2, C29.2, C30.2, C31.2, C32.2, C33.2, C34.2, J2.8, J2.SH, J4.8, J4.SH, J5.8, J5.SH, R4.1, R5.1, U5.3 (GNDA), U5.17 (GNDA), U5.22 (GNDD), U5.26 (GNDD), U5.32 (GNDD), U5.38 (GNDD), U5.57 (GNDD), U5.62 (GNDA), U5.65 (EXP), Y1.2 (G), Y1.4 (G); also elsewhere on the board
unnamed: J2.9, R8.1
unnamed: J2.10, R12.1
unnamed: J2.11, R13.1
unnamed: J2.12, R7.1
unnamed: C27.1, J2.5 (RCT)
unnamed: C26.1, J2.4 (TCT)
unnamed: J4.9, R15.1
unnamed: J4.10, R18.1
unnamed: J4.11, R19.1
unnamed: J4.12, R14.1
unnamed: C29.1, J4.5 (RCT)
unnamed: C28.1, J4.4 (TCT)
unnamed: J5.9, R17.1
unnamed: J5.10, R22.1
unnamed: J5.11, R23.1
unnamed: J5.12, R16.1
unnamed: C31.1, J5.5 (RCT)
unnamed: C30.1, J5.4 (TCT)
unnamed: R4.2, U5.61 (ISET)
unnamed: R12.2, U5.51 (LED1_0)
unnamed: R13.2, U5.50 (LED1_1)
unnamed: R18.2, U5.49 (LED2_0)
unnamed: R19.2, U5.48 (LED2_1)
unnamed: R22.2, U5.20 (LED3_0)
unnamed: R23.2, U5.19 (LED3_1)
unnamed: C20.1, U5.63 (XI), Y1.1
unnamed: C24.1, U5.64 (XO), Y1.3
VDD12D: C14.1, C15.1, C16.1, C17.1, FB4.1, U5.21 (VDD12D), U5.33 (VDD12D), U5.59 (VDD12D)
VDDAT: C2.1, C3.1, C4.1, C6.1, C7.1, C8.1, C33.1, FB5.1, U5.2 (VDDAT), U5.12 (VDDAT), U5.60 (VDDAT)
VDDIO: C10.1, C11.1, C18.1, C19.1, FB1.1, U5.27 (VDDIO), U5.39 (VDDIO), U5.56 (VDDIO)

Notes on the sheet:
pin 2,12,60
Place small C near pin

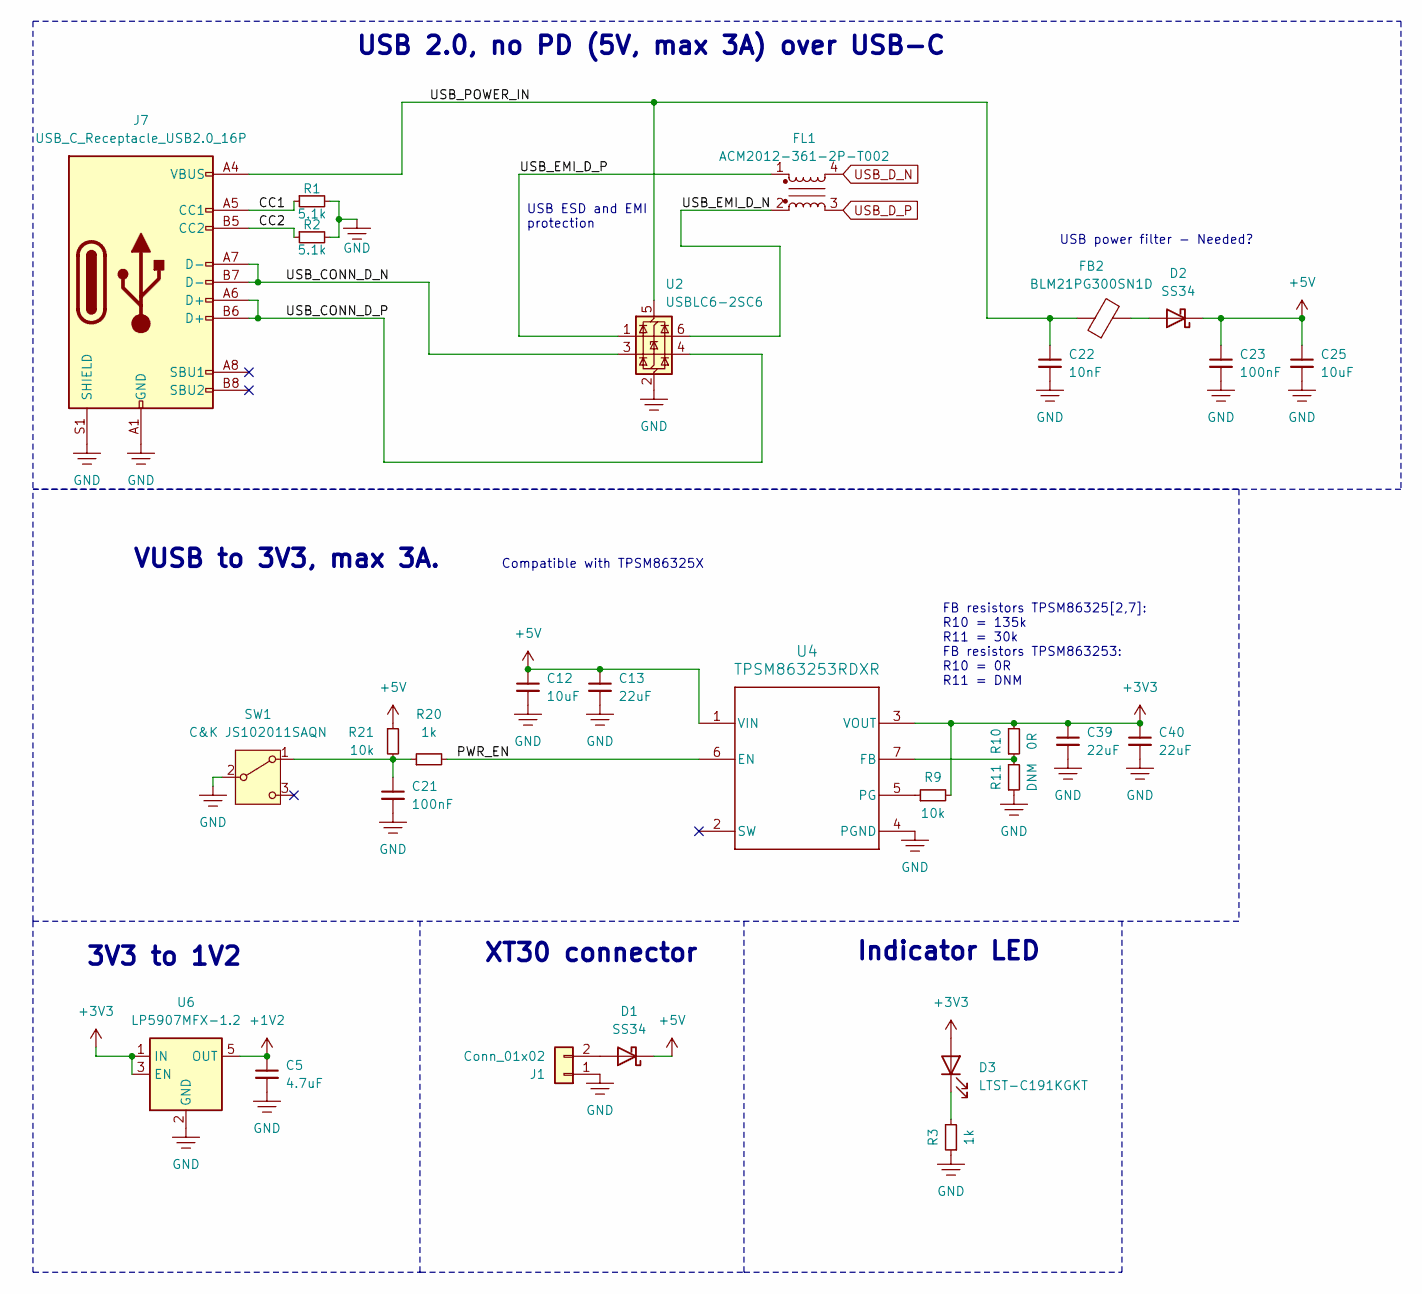
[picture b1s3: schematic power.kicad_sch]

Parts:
C5: 4.7uF; C_0603_1608Metric
C12, C25: 10uF; C_0805_2012Metric; LCSC C15850
C13, C39, C40: 22uF; C_0805_2012Metric; LCSC C45783
C21, C23: 100nF; C_0402_1005Metric; LCSC C1525
C22: 10nF; C_0402_1005Metric; LCSC C15195
D1, D2: SS34; D_SMA
D3: LTST-C191KGKT; LED_0603_1608Metric
FB2: BLM21PG300SN1D; R_0805_2012Metric; LCSC C16903
FL1: ACM2012-361-2P-T002; ACM2012_TDK
J1: Conn_01x02; AMASS_XT30U-F_1x02_P5.0mm_Vertical
J7: USB_C_Receptacle_USB2.0_16P; USB_C_Receptacle_GCT_USB4110
R1, R2: 5.1k; R_0402_1005Metric; LCSC C258132
R3: 1k; R_0402_1005Metric; LCSC C140214
R9, R21: 10k; R_0402_1005Metric; LCSC C140214
R10: 0R; R_0402_1005Metric; LCSC C279984
R11: DNM; R_0402_1005Metric; LCSC C279984
R20: 1k; R_0402_1005Metric; LCSC C279981
SW1: C&K JS102011SAQN; SW_SPDT_CK_JS102011SAQN
U2: USBLC6-2SC6; SOT-23-6; LCSC C5250994
U4: TPSM863253RDXR; RDX0007A-MFG
U6: LP5907MFX-1.2; SOT-23-5

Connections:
+1V2: C5.1, U6.5 (OUT); also elsewhere on the board
+3V3: C39.1, C40.1, D3.2 (A), R9.2, R10.2, U4.3 (VOUT), U6.1 (IN), U6.3 (EN); also elsewhere on the board
+5V: C12.1, C13.1, C23.1, C25.1, D1.1 (K), D2.1 (K), R21.1, U4.1 (VIN)
/power/CC1: J7.A5 (CC1), R1.1
/power/CC2: J7.B5 (CC2), R2.1
/power/PWR_EN: R20.2, U4.6 (EN)
/power/USB_CONN_D_N: J7.A7 (D-), J7.B7 (D-), U2.3 (I/O2)
/power/USB_CONN_D_P: J7.A6 (D+), J7.B6 (D+), U2.4 (I/O2)
/power/USB_EMI_D_N: FL1.2, U2.6 (I/O1)
/power/USB_EMI_D_P: FL1.1, U2.1 (I/O1)
/power/USB_POWER_IN: C22.1, FB2.1, J7.A4 (VBUS), J7.A9 (VBUS), J7.B4 (VBUS), J7.B9 (VBUS), U2.5 (VBUS)
GND: C5.2, C12.2, C13.2, C21.2, C22.2, C23.2, C25.2, C39.2, C40.2, J1.1, J7.A1 (GND), J7.A12 (GND), J7.B1 (GND), J7.B12 (GND), J7.S1 (SHIELD), R1.2, R2.2, R3.1, R11.1, SW1.2 (B), U2.2 (GND), U4.4 (PGND), U6.2 (GND); also elsewhere on the board
unnamed: D1.2 (A), J1.2
unnamed: D2.2 (A), FB2.2
unnamed: D3.1 (K), R3.2
unnamed: C21.1, R20.1, R21.2, SW1.1 (A)
unnamed: R10.1, R11.2, U4.7 (FB)
unnamed: R9.1, U4.5 (PG)
USB_D_N: FL1.4; also elsewhere on the board
USB_D_P: FL1.3; also elsewhere on the board

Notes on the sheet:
XT30 connector
Compatible with TPSM86325X
FB resistors TPSM86325[2,7]: R10 = 135k R11 = 30k FB resistors TPSM863253: R10 = 0R R11 = DNM
Indicator LED
3V3 to 1V2
USB ESD and EMI protection
USB 2.0, no PD (5V, max 3A) over USB-C
USB power filter - Needed?
VUSB to 3V3, max 3A.

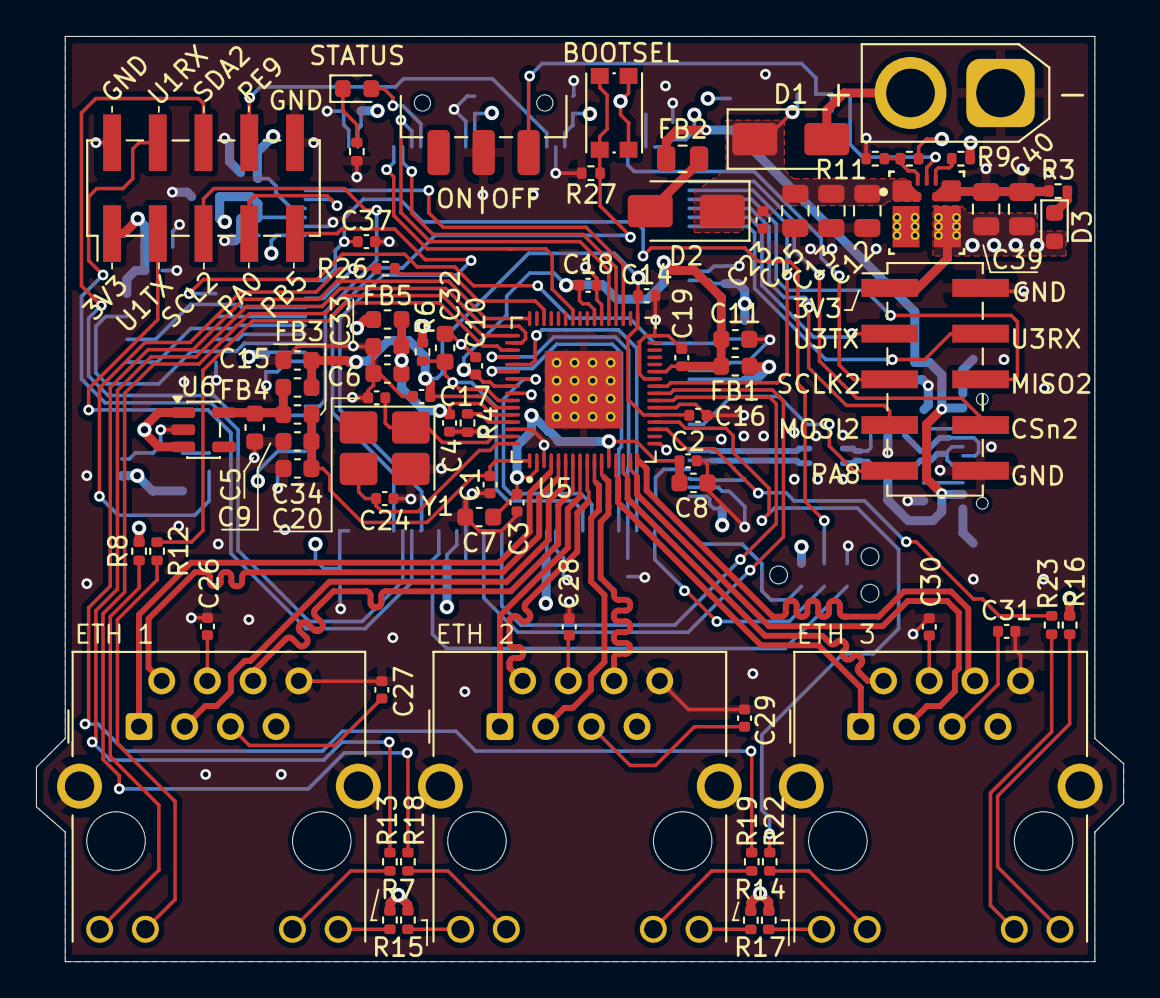
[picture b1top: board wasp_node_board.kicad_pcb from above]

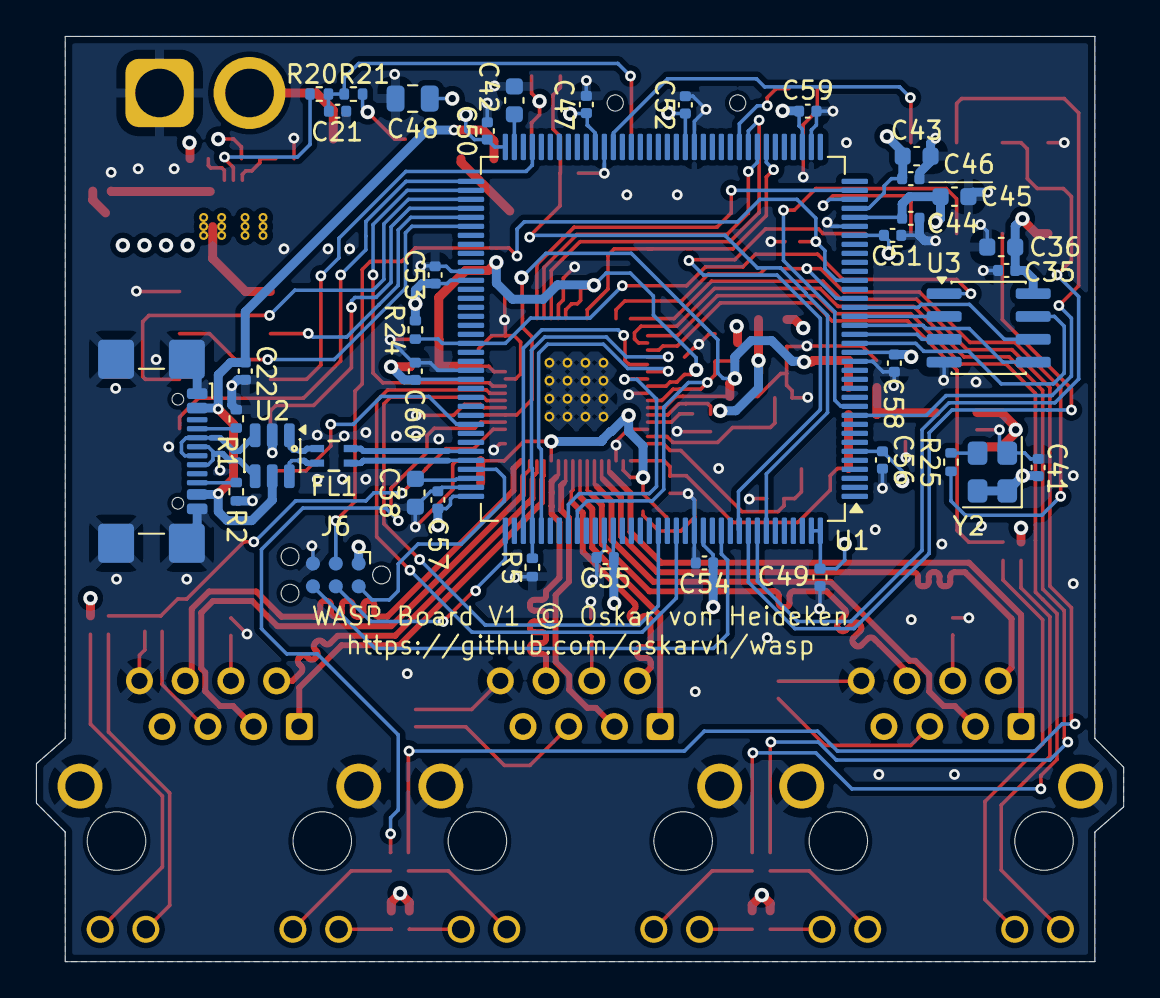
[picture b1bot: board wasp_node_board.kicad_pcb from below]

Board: 4 copper layers, 60.4 x 51.4 mm, 116 parts (39 on the bottom side), 107 nets.

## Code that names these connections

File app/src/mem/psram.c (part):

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		return -EIO;
	}

	/* Port 1, low IO bank: CLK PF10, NCS PG6, IO0-3 PF8/PF9/PF7/PF6. */
	ospim.ClkPort = 1;
	ospim.NCSPort = 1;
	ospim.IOLowPort = HAL_OSPIM_IOPORT_1_LOW;
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

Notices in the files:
app/src/mem/psram.c:
Copyright (c) 2026 Oskar von Heideken
SPDX-License-Identifier: Apache-2.0
hardware/wasp_node_board/wasp_node_board.kicad_pcb:
WASP Board V1 © Oskar von Heideken
